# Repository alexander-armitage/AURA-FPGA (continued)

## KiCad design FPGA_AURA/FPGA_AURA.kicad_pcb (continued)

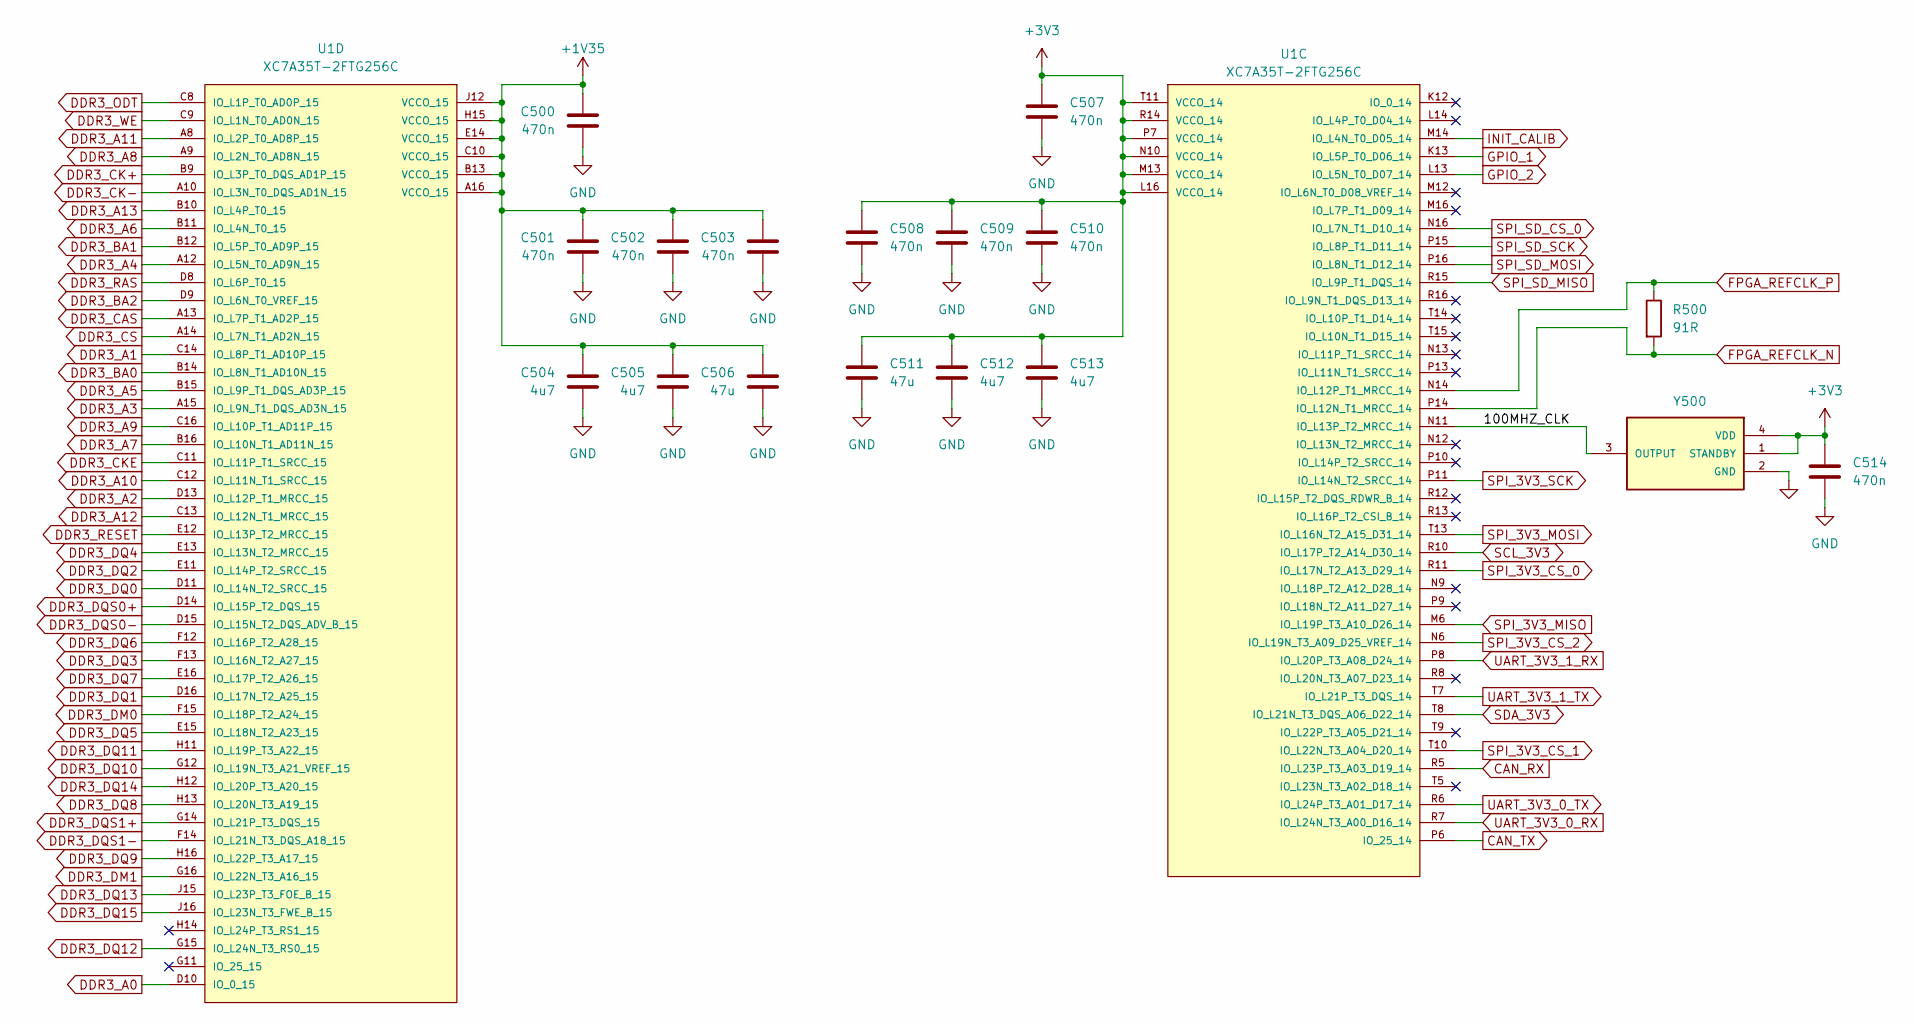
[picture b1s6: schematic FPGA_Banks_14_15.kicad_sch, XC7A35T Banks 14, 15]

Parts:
C500, C501, C502, C503, C507, C508, C509, C510, C514: 470n; C_0402_1005Metric
C504, C505, C512, C513: 4u7; C_0603_1608Metric
C506, C511: 47u; C_0603_1608Metric
R500: 91R; R_0201_0603Metric
U1: XC7A35T-2FTG256C; BGA256C100P16X16_1700X1700X155
Y500: ASEM1-100.000MHZ-LC-T; XTAL_ASEM1-100.000MHZ-LC-T; PARTREV 1.4.2021

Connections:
+1V35: C500.1, C501.1, C502.1, C503.1, C504.1, C505.1, C506.1, U1.A16 (VCCO_15), U1.B13 (VCCO_15), U1.C10 (VCCO_15), U1.E14 (VCCO_15), U1.H15 (VCCO_15), U1.J12 (VCCO_15); also elsewhere on the board
+3V3: C507.1, C508.1, C509.1, C510.1, C511.1, C512.1, C513.1, C514.1, U1.L16 (VCCO_14), U1.M13 (VCCO_14), U1.N10 (VCCO_14), U1.P7 (VCCO_14), U1.R14 (VCCO_14), U1.T11 (VCCO_14), Y500.1 (STANDBY), Y500.4 (VDD); also elsewhere on the board
/500_FPGA_Banks_14_15/100MHZ_CLK: U1.N11 (IO_L13P_T2_MRCC_14), Y500.3 (OUTPUT)
CAN_RX: U1.R5 (IO_L23P_T3_A03_D19_14); also elsewhere on the board
CAN_TX: U1.P6 (IO_25_14); also elsewhere on the board
DDR3_A0: U1.D10 (IO_0_15); also elsewhere on the board
DDR3_A1: U1.C14 (IO_L8P_T1_AD10P_15); also elsewhere on the board
DDR3_A2: U1.D13 (IO_L12P_T1_MRCC_15); also elsewhere on the board
DDR3_A3: U1.A15 (IO_L9N_T1_DQS_AD3N_15); also elsewhere on the board
DDR3_A4: U1.A12 (IO_L5N_T0_AD9N_15); also elsewhere on the board
DDR3_A5: U1.B15 (IO_L9P_T1_DQS_AD3P_15); also elsewhere on the board
DDR3_A6: U1.B11 (IO_L4N_T0_15); also elsewhere on the board
DDR3_A7: U1.B16 (IO_L10N_T1_AD11N_15); also elsewhere on the board
DDR3_A8: U1.A9 (IO_L2N_T0_AD8N_15); also elsewhere on the board
DDR3_A9: U1.C16 (IO_L10P_T1_AD11P_15); also elsewhere on the board
DDR3_A10: U1.C12 (IO_L11N_T1_SRCC_15); also elsewhere on the board
DDR3_A11: U1.A8 (IO_L2P_T0_AD8P_15); also elsewhere on the board
DDR3_A12: U1.C13 (IO_L12N_T1_MRCC_15); also elsewhere on the board
DDR3_A13: U1.B10 (IO_L4P_T0_15); also elsewhere on the board
DDR3_BA0: U1.B14 (IO_L8N_T1_AD10N_15); also elsewhere on the board
DDR3_BA1: U1.B12 (IO_L5P_T0_AD9P_15); also elsewhere on the board
DDR3_BA2: U1.D9 (IO_L6N_T0_VREF_15); also elsewhere on the board
DDR3_CAS: U1.A13 (IO_L7P_T1_AD2P_15); also elsewhere on the board
DDR3_CK+: U1.B9 (IO_L3P_T0_DQS_AD1P_15); also elsewhere on the board
DDR3_CK-: U1.A10 (IO_L3N_T0_DQS_AD1N_15); also elsewhere on the board
DDR3_CKE: U1.C11 (IO_L11P_T1_SRCC_15); also elsewhere on the board
DDR3_CS: U1.A14 (IO_L7N_T1_AD2N_15); also elsewhere on the board
DDR3_DM0: U1.F15 (IO_L18P_T2_A24_15); also elsewhere on the board
DDR3_DM1: U1.G16 (IO_L22N_T3_A16_15); also elsewhere on the board
DDR3_DQ0: U1.D11 (IO_L14N_T2_SRCC_15); also elsewhere on the board
DDR3_DQ1: U1.D16 (IO_L17N_T2_A25_15); also elsewhere on the board
DDR3_DQ2: U1.E11 (IO_L14P_T2_SRCC_15); also elsewhere on the board
DDR3_DQ3: U1.F13 (IO_L16N_T2_A27_15); also elsewhere on the board
DDR3_DQ4: U1.E13 (IO_L13N_T2_MRCC_15); also elsewhere on the board
DDR3_DQ5: U1.E15 (IO_L18N_T2_A23_15); also elsewhere on the board
DDR3_DQ6: U1.F12 (IO_L16P_T2_A28_15); also elsewhere on the board
DDR3_DQ7: U1.E16 (IO_L17P_T2_A26_15); also elsewhere on the board
DDR3_DQ8: U1.H13 (IO_L20N_T3_A19_15); also elsewhere on the board
DDR3_DQ9: U1.H16 (IO_L22P_T3_A17_15); also elsewhere on the board
DDR3_DQ10: U1.G12 (IO_L19N_T3_A21_VREF_15); also elsewhere on the board
DDR3_DQ11: U1.H11 (IO_L19P_T3_A22_15); also elsewhere on the board
DDR3_DQ12: U1.G15 (IO_L24N_T3_RS0_15); also elsewhere on the board
DDR3_DQ13: U1.J15 (IO_L23P_T3_FOE_B_15); also elsewhere on the board
DDR3_DQ14: U1.H12 (IO_L20P_T3_A20_15); also elsewhere on the board
DDR3_DQ15: U1.J16 (IO_L23N_T3_FWE_B_15); also elsewhere on the board
DDR3_DQS0+: U1.D14 (IO_L15P_T2_DQS_15); also elsewhere on the board
DDR3_DQS0-: U1.D15 (IO_L15N_T2_DQS_ADV_B_15); also elsewhere on the board
DDR3_DQS1+: U1.G14 (IO_L21P_T3_DQS_15); also elsewhere on the board
DDR3_DQS1-: U1.F14 (IO_L21N_T3_DQS_A18_15); also elsewhere on the board
DDR3_ODT: U1.C8 (IO_L1P_T0_AD0P_15); also elsewhere on the board
DDR3_RAS: U1.D8 (IO_L6P_T0_15); also elsewhere on the board
DDR3_RESET: U1.E12 (IO_L13P_T2_MRCC_15); also elsewhere on the board
DDR3_WE: U1.C9 (IO_L1N_T0_AD0N_15); also elsewhere on the board
FPGA_REFCLK_N: R500.2, U1.P14 (IO_L12N_T1_MRCC_14); also elsewhere on the board
FPGA_REFCLK_P: R500.1, U1.N14 (IO_L12P_T1_MRCC_14); also elsewhere on the board
GND: C500.2, C501.2, C502.2, C503.2, C504.2, C505.2, C506.2, C507.2, C508.2, C509.2, C510.2, C511.2, C512.2, C513.2, C514.2, Y500.2 (GND); also elsewhere on the board
GPIO_1: U1.K13 (IO_L5P_T0_D06_14); also elsewhere on the board
GPIO_2: U1.L13 (IO_L5N_T0_D07_14); also elsewhere on the board
INIT_CALIB: U1.M14 (IO_L4N_T0_D05_14); also elsewhere on the board
SCL_3V3: U1.R10 (IO_L17P_T2_A14_D30_14); also elsewhere on the board
SDA_3V3: U1.T8 (IO_L21N_T3_DQS_A06_D22_14); also elsewhere on the board
SPI_3V3_CS_0: U1.R11 (IO_L17N_T2_A13_D29_14); also elsewhere on the board
SPI_3V3_CS_1: U1.T10 (IO_L22N_T3_A04_D20_14); also elsewhere on the board
SPI_3V3_CS_2: U1.N6 (IO_L19N_T3_A09_D25_VREF_14); also elsewhere on the board
SPI_3V3_MISO: U1.M6 (IO_L19P_T3_A10_D26_14); also elsewhere on the board
SPI_3V3_MOSI: U1.T13 (IO_L16N_T2_A15_D31_14); also elsewhere on the board
SPI_3V3_SCK: U1.P11 (IO_L14N_T2_SRCC_14); also elsewhere on the board
SPI_SD_CS_0: U1.N16 (IO_L7N_T1_D10_14); also elsewhere on the board
SPI_SD_MISO: U1.R15 (IO_L9P_T1_DQS_14); also elsewhere on the board
SPI_SD_MOSI: U1.P16 (IO_L8N_T1_D12_14); also elsewhere on the board
SPI_SD_SCK: U1.P15 (IO_L8P_T1_D11_14); also elsewhere on the board
UART_3V3_0_RX: U1.R7 (IO_L24N_T3_A00_D16_14); also elsewhere on the board
UART_3V3_0_TX: U1.R6 (IO_L24P_T3_A01_D17_14); also elsewhere on the board
UART_3V3_1_RX: U1.P8 (IO_L20P_T3_A08_D24_14); also elsewhere on the board
UART_3V3_1_TX: U1.T7 (IO_L21P_T3_DQS_14); also elsewhere on the board

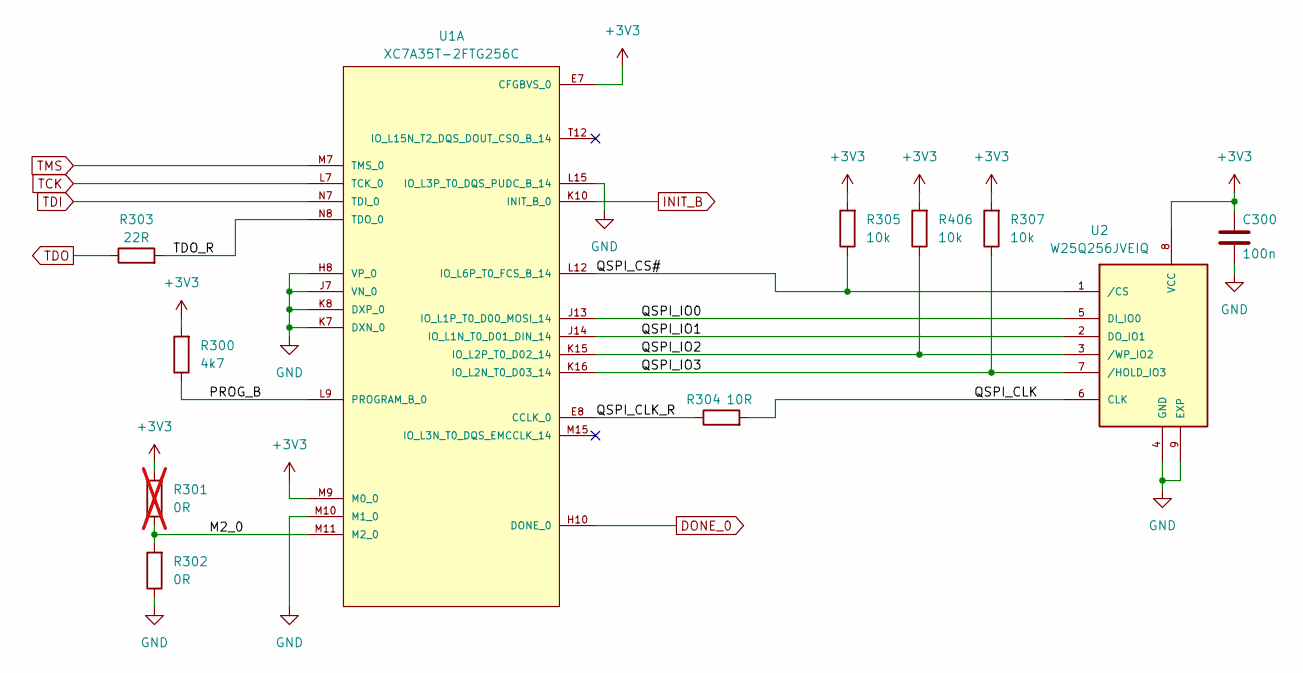
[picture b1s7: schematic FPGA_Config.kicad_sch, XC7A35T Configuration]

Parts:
C300: 100n; C_0402_1005Metric
R300: 4k7; R_0402_1005Metric
R301: 0R; R_0402_1005Metric; not fitted
R302: 0R; R_0402_1005Metric
R303: 22R; R_0402_1005Metric
R304: 10R; R_0402_1005Metric
R305, R307, R406: 10k; R_0402_1005Metric
U1: XC7A35T-2FTG256C; BGA256C100P16X16_1700X1700X155
U2: W25Q256JVEIQ; SON127P800X600X80-9N; MOUSER_PART_NUMBER 454-W25Q256JVEIQ

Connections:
+3V3: C300.1, R300.2, R301.2, R305.2, R307.2, R406.2, U1.E7 (CFGBVS_0), U1.M9 (M0_0), U2.8 (VCC); also elsewhere on the board
/300_FPGA_Config/M2_0: R301.1, R302.2, U1.M11 (M2_0)
/300_FPGA_Config/PROG_B: R300.1, U1.L9 (PROGRAM_B_0)
/300_FPGA_Config/QSPI_CLK: R304.2, U2.6 (CLK)
/300_FPGA_Config/QSPI_CLK_R: R304.1, U1.E8 (CCLK_0)
/300_FPGA_Config/QSPI_CS#: R305.1, U1.L12 (IO_L6P_T0_FCS_B_14), U2.1 (/CS)
/300_FPGA_Config/QSPI_IO0: U1.J13 (IO_L1P_T0_D00_MOSI_14), U2.5 (DI_IO0)
/300_FPGA_Config/QSPI_IO1: U1.J14 (IO_L1N_T0_D01_DIN_14), U2.2 (DO_IO1)
/300_FPGA_Config/QSPI_IO2: R406.1, U1.K15 (IO_L2P_T0_D02_14), U2.3 (/WP_IO2)
/300_FPGA_Config/QSPI_IO3: R307.1, U1.K16 (IO_L2N_T0_D03_14), U2.7 (/HOLD_IO3)
/300_FPGA_Config/TDO_R: R303.2, U1.N8 (TDO_0)
DONE_0: U1.H10 (DONE_0); also elsewhere on the board
GND: C300.2, R302.1, U1.H8 (VP_0), U1.J7 (VN_0), U1.K7 (DXN_0), U1.K8 (DXP_0), U1.L15 (IO_L3P_T0_DQS_PUDC_B_14), U1.M10 (M1_0), U2.4 (GND), U2.9 (EXP); also elsewhere on the board
INIT_B: U1.K10 (INIT_B_0); also elsewhere on the board
TCK: U1.L7 (TCK_0); also elsewhere on the board
TDI: U1.N7 (TDI_0); also elsewhere on the board
TDO: R303.1; also elsewhere on the board
TMS: U1.M7 (TMS_0); also elsewhere on the board

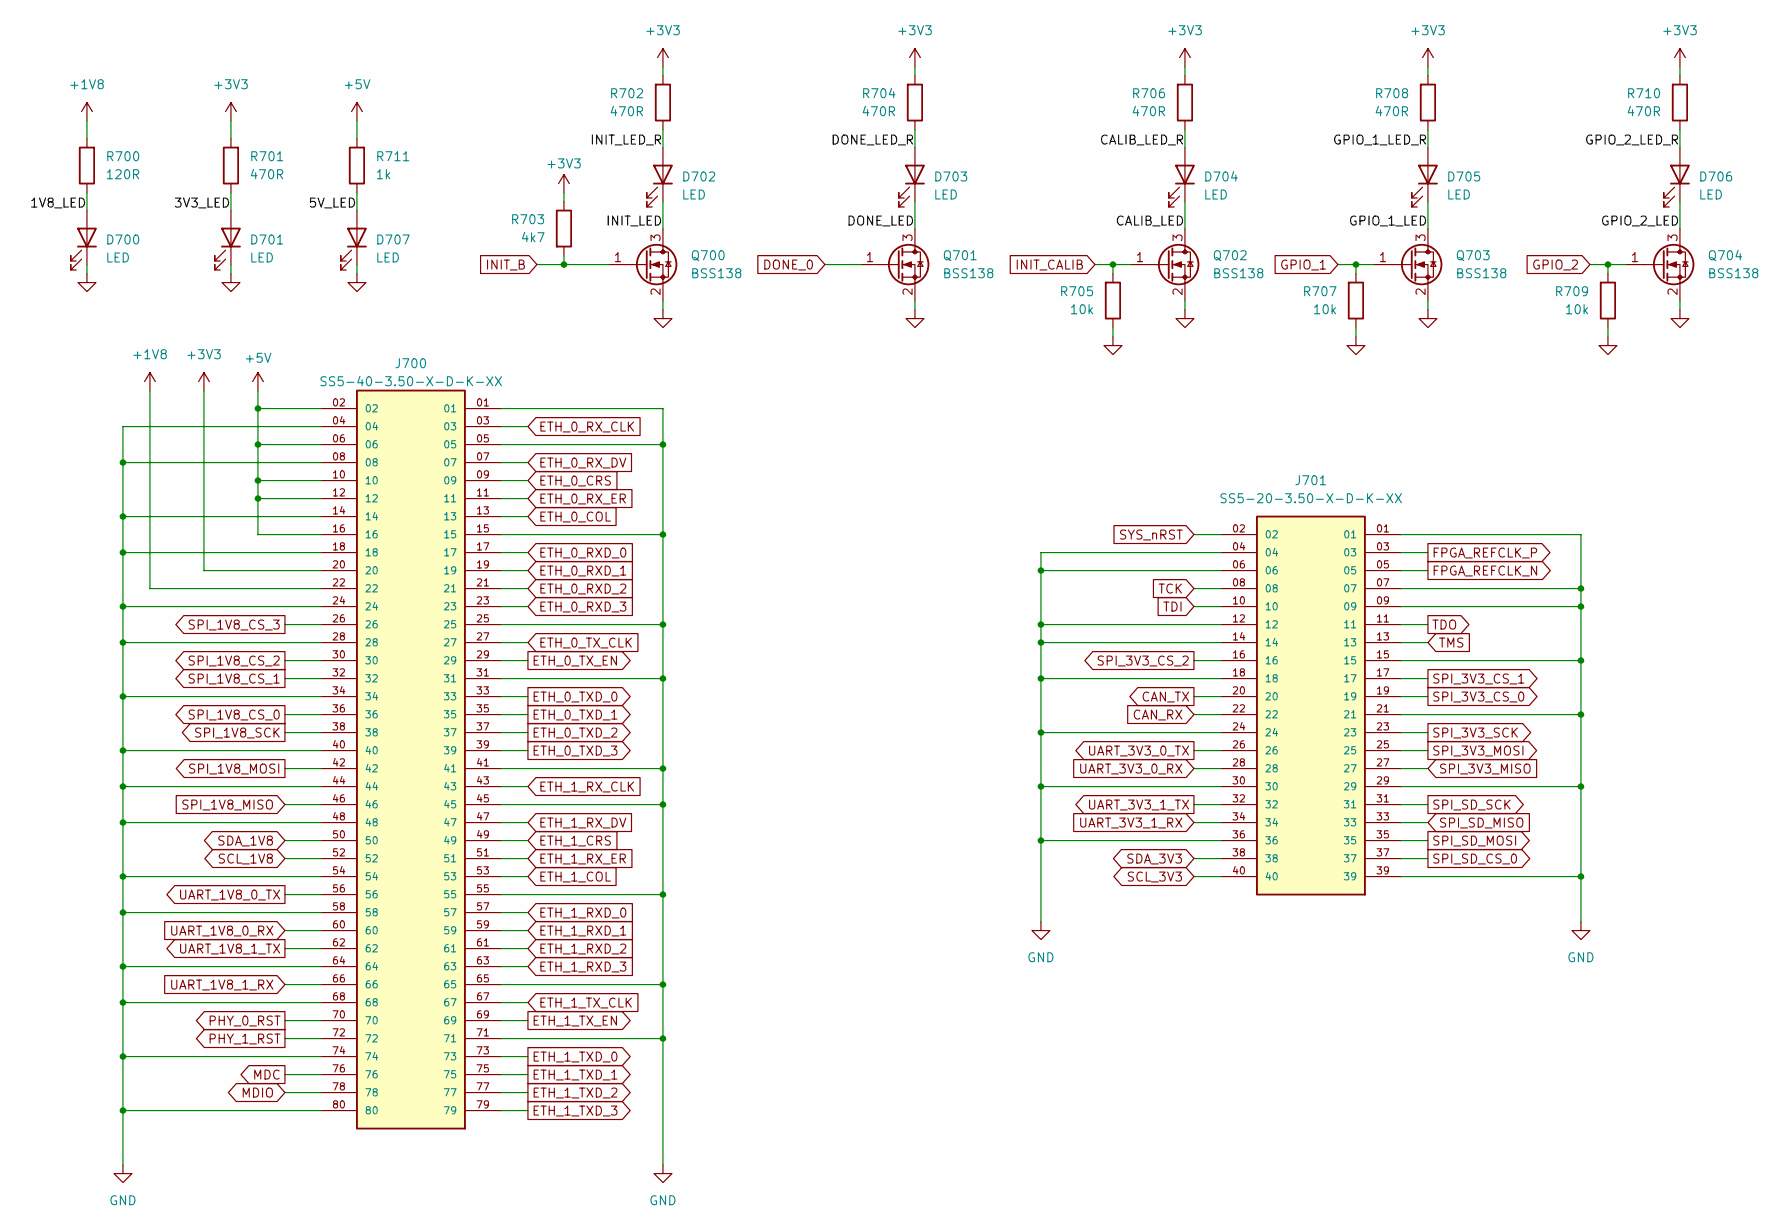
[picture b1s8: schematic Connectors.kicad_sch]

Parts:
D700, D701, D702, D703, D704, D705, D706, D707: LED; LED_0603_1608Metric
J700: SS5-40-3.50-X-D-K-XX; SAMTEC_SS5-40-3.50-X-D-K-XX; PARTREV F
J701: SS5-20-3.50-X-D-K-XX; SAMTEC_SS5-20-3.50-X-D-K-XX; PARTREV F
Q700, Q701, Q702, Q703, Q704: BSS138; SOT-23
R700: 120R; R_0402_1005Metric
R701, R702, R704, R706, R708, R710: 470R; R_0402_1005Metric
R703: 4k7; R_0402_1005Metric
R705, R707, R709: 10k; R_0402_1005Metric
R711: 1k; R_0402_1005Metric

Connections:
+1V8: J700.22, R700.2; also elsewhere on the board
+3V3: J700.20, R701.2, R702.2, R703.1, R704.2, R706.2, R708.2, R710.2; also elsewhere on the board
+5V: J700.02, J700.06, J700.10, J700.12, J700.16, R711.2; also elsewhere on the board
/700_Connectors/1V8_LED: D700.2 (A), R700.1
/700_Connectors/3V3_LED: D701.2 (A), R701.1
/700_Connectors/5V_LED: D707.2 (A), R711.1
/700_Connectors/CALIB_LED: D704.1 (K), Q702.3 (D)
/700_Connectors/CALIB_LED_R: D704.2 (A), R706.1
/700_Connectors/DONE_LED: D703.1 (K), Q701.3 (D)
/700_Connectors/DONE_LED_R: D703.2 (A), R704.1
/700_Connectors/GPIO_1_LED: D705.1 (K), Q703.3 (D)
/700_Connectors/GPIO_1_LED_R: D705.2 (A), R708.1
/700_Connectors/GPIO_2_LED: D706.1 (K), Q704.3 (D)
/700_Connectors/GPIO_2_LED_R: D706.2 (A), R710.1
/700_Connectors/INIT_LED: D702.1 (K), Q700.3 (D)
/700_Connectors/INIT_LED_R: D702.2 (A), R702.1
CAN_RX: J701.22; also elsewhere on the board
CAN_TX: J701.20; also elsewhere on the board
DONE_0: Q701.1 (G); also elsewhere on the board
ETH_0_COL: J700.13; also elsewhere on the board
ETH_0_CRS: J700.09; also elsewhere on the board
ETH_0_RXD_0: J700.17; also elsewhere on the board
ETH_0_RXD_1: J700.19; also elsewhere on the board
ETH_0_RXD_2: J700.21; also elsewhere on the board
ETH_0_RXD_3: J700.23; also elsewhere on the board
ETH_0_RX_CLK: J700.03; also elsewhere on the board
ETH_0_RX_DV: J700.07; also elsewhere on the board
ETH_0_RX_ER: J700.11; also elsewhere on the board
ETH_0_TXD_0: J700.33; also elsewhere on the board
ETH_0_TXD_1: J700.35; also elsewhere on the board
ETH_0_TXD_2: J700.37; also elsewhere on the board
ETH_0_TXD_3: J700.39; also elsewhere on the board
ETH_0_TX_CLK: J700.27; also elsewhere on the board
ETH_0_TX_EN: J700.29; also elsewhere on the board
ETH_1_COL: J700.53; also elsewhere on the board
ETH_1_CRS: J700.49; also elsewhere on the board
ETH_1_RXD_0: J700.57; also elsewhere on the board
ETH_1_RXD_1: J700.59; also elsewhere on the board
ETH_1_RXD_2: J700.61; also elsewhere on the board
ETH_1_RXD_3: J700.63; also elsewhere on the board
ETH_1_RX_CLK: J700.43; also elsewhere on the board
ETH_1_RX_DV: J700.47; also elsewhere on the board
ETH_1_RX_ER: J700.51; also elsewhere on the board
ETH_1_TXD_0: J700.73; also elsewhere on the board
ETH_1_TXD_1: J700.75; also elsewhere on the board
ETH_1_TXD_2: J700.77; also elsewhere on the board
ETH_1_TXD_3: J700.79; also elsewhere on the board
ETH_1_TX_CLK: J700.67; also elsewhere on the board
ETH_1_TX_EN: J700.69; also elsewhere on the board
FPGA_REFCLK_N: J701.05; also elsewhere on the board
FPGA_REFCLK_P: J701.03; also elsewhere on the board
GND: D700.1 (K), D701.1 (K), D707.1 (K), J700.01, J700.04, J700.05, J700.08, J700.14, J700.15, J700.18, J700.24, J700.25, J700.28, J700.31, J700.34, J700.40, J700.41, J700.44, J700.45, J700.48, J700.54, J700.55, J700.58, J700.64, J700.65, J700.68, J700.71, J700.74, J700.80, J701.01, J701.04, J701.06, J701.07, J701.09, J701.12, J701.14, J701.15, J701.18, J701.21, J701.24, J701.29, J701.30, J701.36, J701.39, Q700.2 (S), Q701.2 (S), Q702.2 (S), Q703.2 (S), Q704.2 (S), R705.1, R707.1, R709.1; also elsewhere on the board
GPIO_1: Q703.1 (G), R707.2; also elsewhere on the board
GPIO_2: Q704.1 (G), R709.2; also elsewhere on the board
INIT_B: Q700.1 (G), R703.2; also elsewhere on the board
INIT_CALIB: Q702.1 (G), R705.2; also elsewhere on the board
MDC: J700.76; also elsewhere on the board
MDIO: J700.78; also elsewhere on the board
PHY_0_RST: J700.70; also elsewhere on the board
PHY_1_RST: J700.72; also elsewhere on the board
SCL_1V8: J700.52; also elsewhere on the board
SCL_3V3: J701.40; also elsewhere on the board
SDA_1V8: J700.50; also elsewhere on the board
SDA_3V3: J701.38; also elsewhere on the board
SPI_1V8_CS_0: J700.36; also elsewhere on the board
SPI_1V8_CS_1: J700.32; also elsewhere on the board
SPI_1V8_CS_2: J700.30; also elsewhere on the board
SPI_1V8_CS_3: J700.26; also elsewhere on the board
SPI_1V8_MISO: J700.46; also elsewhere on the board
SPI_1V8_MOSI: J700.42; also elsewhere on the board
SPI_1V8_SCK: J700.38; also elsewhere on the board
SPI_3V3_CS_0: J701.19; also elsewhere on the board
SPI_3V3_CS_1: J701.17; also elsewhere on the board
SPI_3V3_CS_2: J701.16; also elsewhere on the board
SPI_3V3_MISO: J701.27; also elsewhere on the board
SPI_3V3_MOSI: J701.25; also elsewhere on the board
SPI_3V3_SCK: J701.23; also elsewhere on the board
SPI_SD_CS_0: J701.37; also elsewhere on the board
SPI_SD_MISO: J701.33; also elsewhere on the board
SPI_SD_MOSI: J701.35; also elsewhere on the board
SPI_SD_SCK: J701.31; also elsewhere on the board
SYS_nRST: J701.02; also elsewhere on the board
TCK: J701.08; also elsewhere on the board
TDI: J701.10; also elsewhere on the board
TDO: J701.11; also elsewhere on the board
TMS: J701.13; also elsewhere on the board
UART_1V8_0_RX: J700.60; also elsewhere on the board
UART_1V8_0_TX: J700.56; also elsewhere on the board
UART_1V8_1_RX: J700.66; also elsewhere on the board
UART_1V8_1_TX: J700.62; also elsewhere on the board
UART_3V3_0_RX: J701.28; also elsewhere on the board
UART_3V3_0_TX: J701.26; also elsewhere on the board
UART_3V3_1_RX: J701.34; also elsewhere on the board
UART_3V3_1_TX: J701.32; also elsewhere on the board

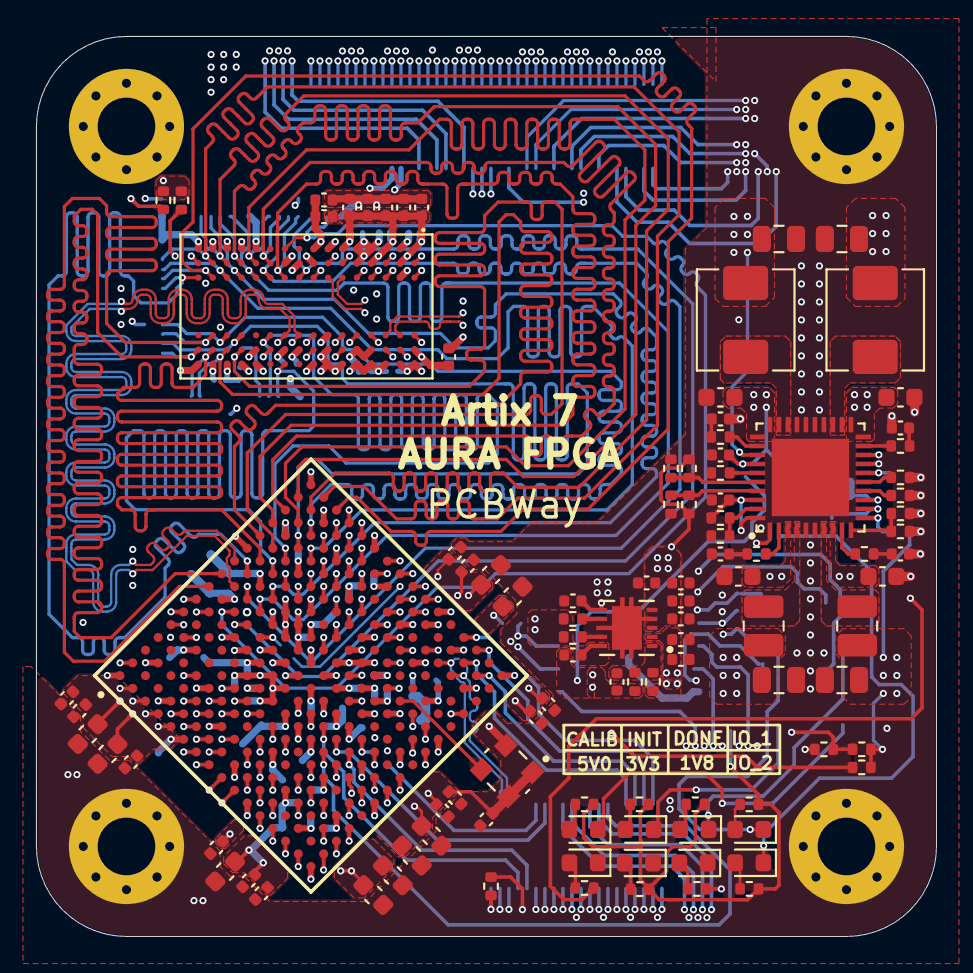
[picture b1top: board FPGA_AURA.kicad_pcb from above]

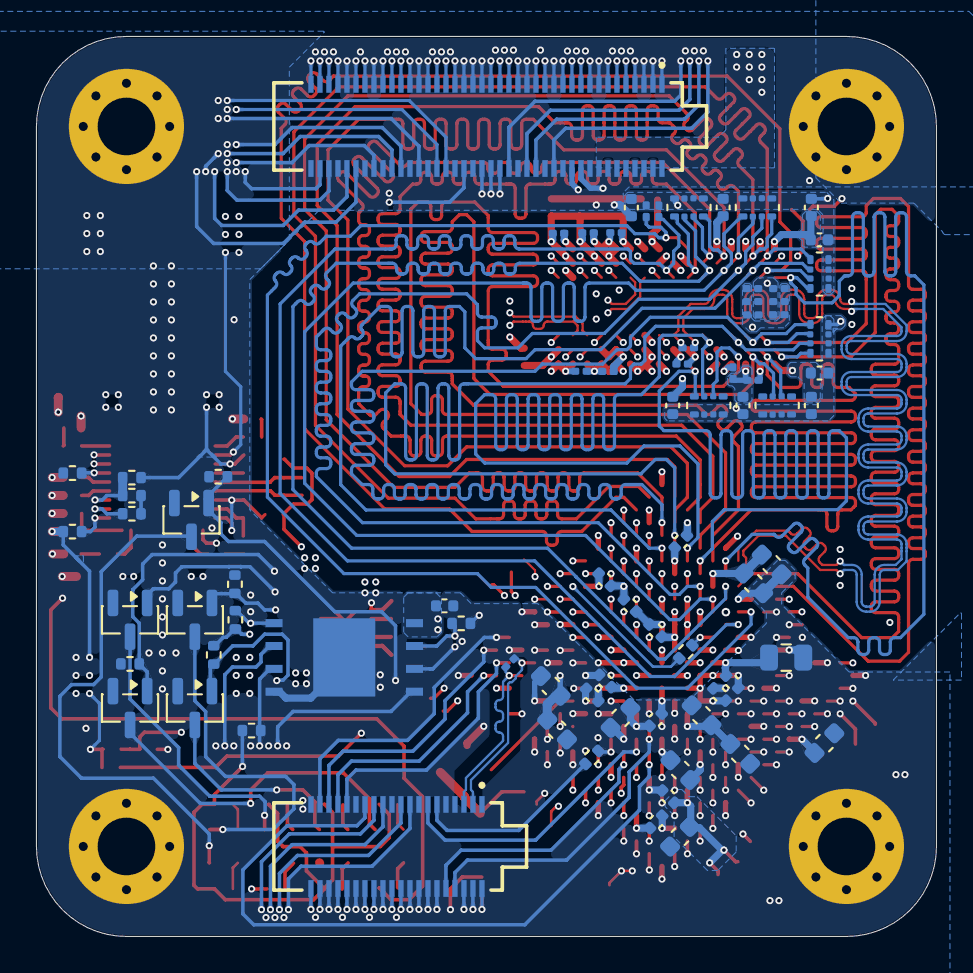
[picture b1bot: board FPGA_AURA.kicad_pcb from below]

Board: 10 copper layers, 50.0 x 50.0 mm, 184 parts (77 on the bottom side), 185 nets.

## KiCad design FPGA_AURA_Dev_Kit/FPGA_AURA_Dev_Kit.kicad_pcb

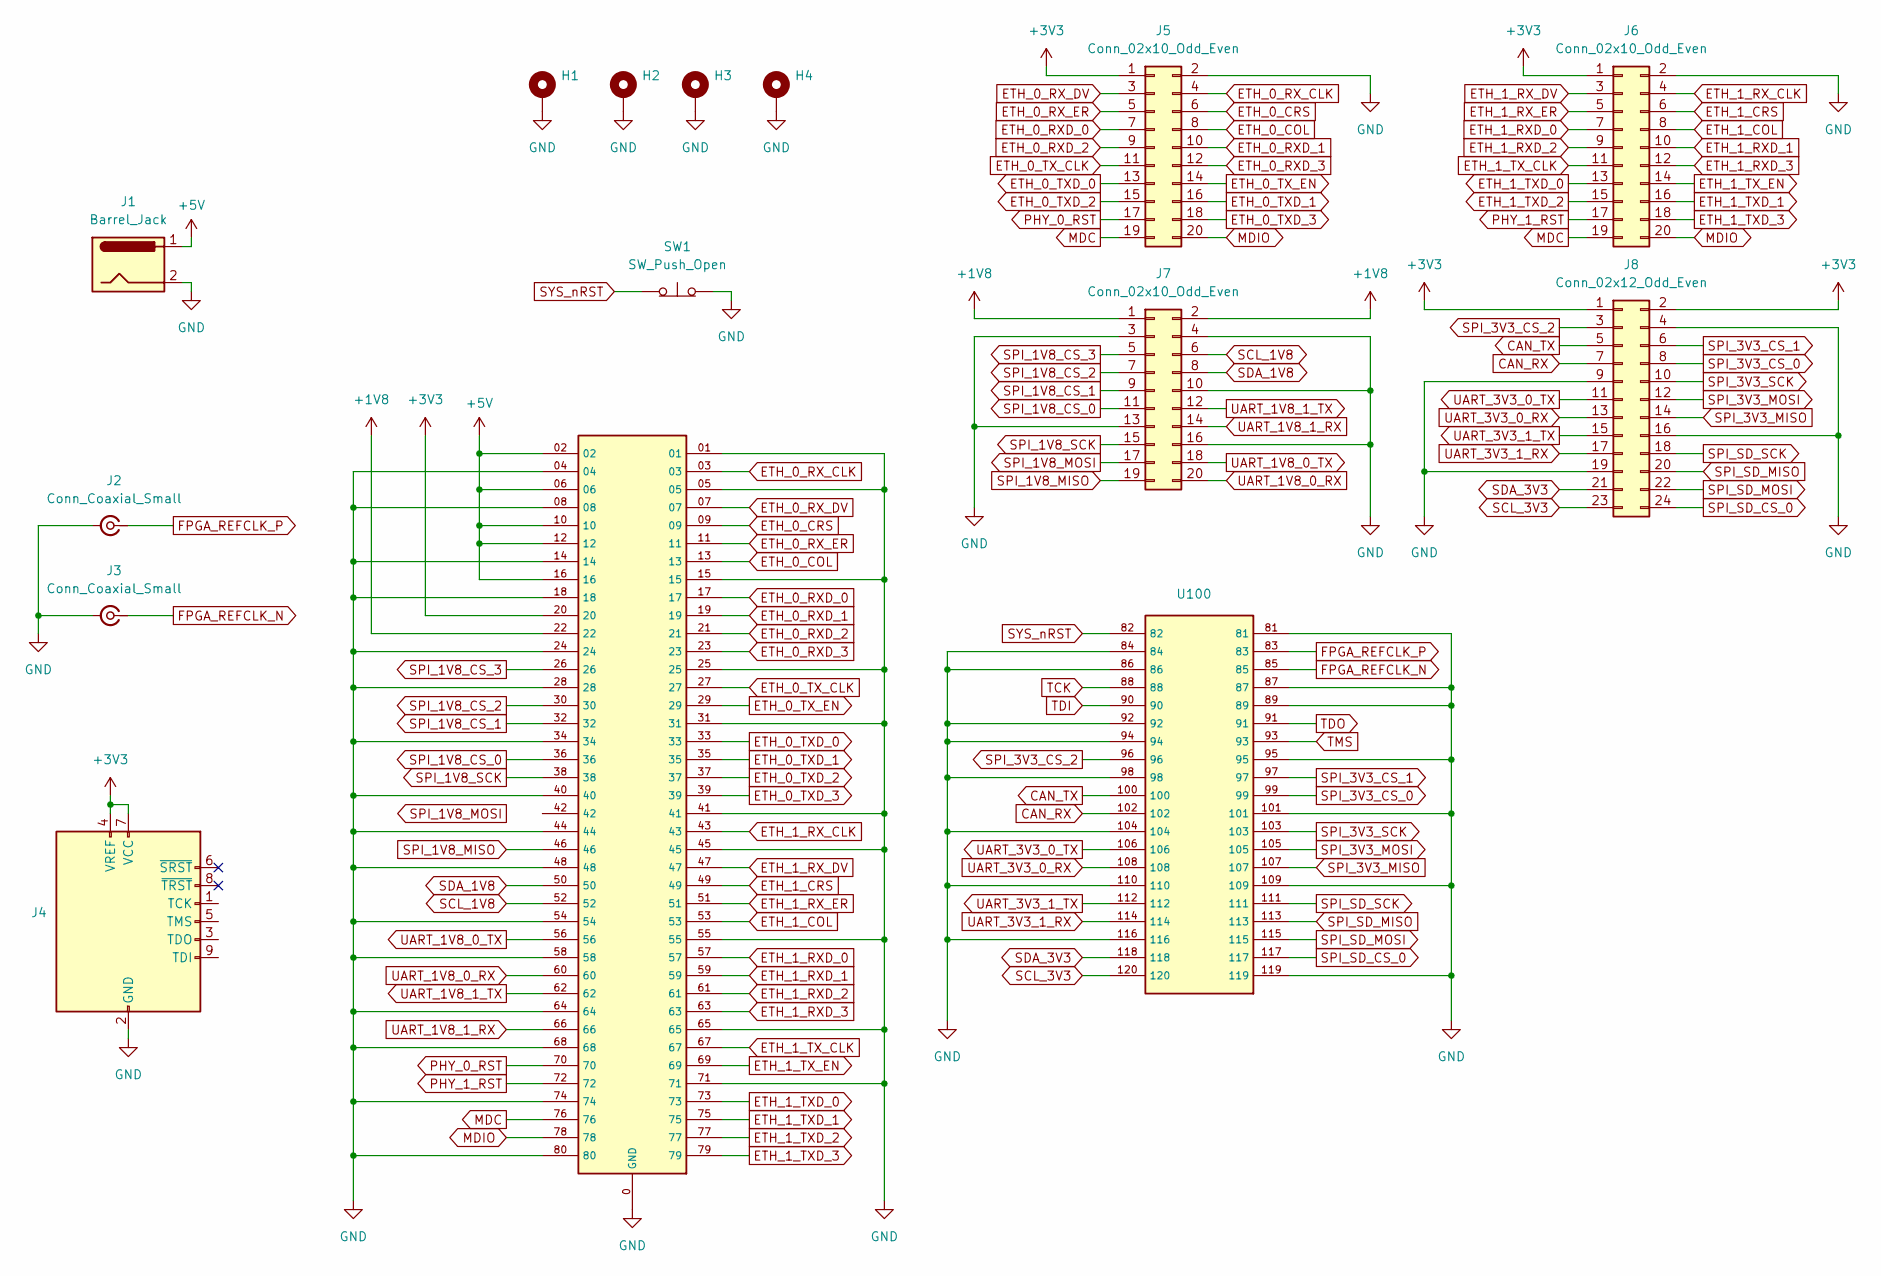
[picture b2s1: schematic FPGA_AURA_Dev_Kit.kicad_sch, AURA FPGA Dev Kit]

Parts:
H1, H2, H3, H4: MountingHole_Pad; MountingHole_3.2mm_M3_Pad_Via
J1: Barrel_Jack; BarrelJack_GCT_DCJ200-10-A_Horizontal
J2, J3: Conn_Coaxial_Small; SMA_Wurth_60312102114405_Vertical
J4: AVR-JTAG-10; SAMESKY_SSK05-BH-254-B5
J5, J6, J7: Conn_02x10_Odd_Even; PinHeader_2x10_P2.54mm_Vertical
J8: Conn_02x12_Odd_Even; PinHeader_2x12_P2.54mm_Vertical
SW1: SW_Push_Open; SW_SPST_CK_RS282G05A3
U100: AURA-FPGA

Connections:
+1V8: J7.1, J7.2, U100.22
+3V3: J4.4 (VREF), J4.7 (VCC), J5.1, J6.1, J8.1, J8.2, U100.20
+5V: J1.1, U100.02, U100.06, U100.10, U100.12, U100.16
CAN_RX: J8.7, U100.102
CAN_TX: J8.5, U100.100
ETH_0_COL: J5.8, U100.13
ETH_0_CRS: J5.6, U100.09
ETH_0_RXD_0: J5.7, U100.17
ETH_0_RXD_1: J5.10, U100.19
ETH_0_RXD_2: J5.9, U100.21
ETH_0_RXD_3: J5.12, U100.23
ETH_0_RX_CLK: J5.4, U100.03
ETH_0_RX_DV: J5.3, U100.07
ETH_0_RX_ER: J5.5, U100.11
ETH_0_TXD_0: J5.13, U100.33
ETH_0_TXD_1: J5.16, U100.35
ETH_0_TXD_2: J5.15, U100.37
ETH_0_TXD_3: J5.18, U100.39
ETH_0_TX_CLK: J5.11, U100.27
ETH_0_TX_EN: J5.14, U100.29
ETH_1_COL: J6.8, U100.53
ETH_1_CRS: J6.6, U100.49
ETH_1_RXD_0: J6.7, U100.57
ETH_1_RXD_1: J6.10, U100.59
ETH_1_RXD_2: J6.9, U100.61
ETH_1_RXD_3: J6.12, U100.63
ETH_1_RX_CLK: J6.4, U100.43
ETH_1_RX_DV: J6.3, U100.47
ETH_1_RX_ER: J6.5, U100.51
ETH_1_TXD_0: J6.13, U100.73
ETH_1_TXD_1: J6.16, U100.75
ETH_1_TXD_2: J6.15, U100.77
ETH_1_TXD_3: J6.18, U100.79
ETH_1_TX_CLK: J6.11, U100.67
ETH_1_TX_EN: J6.14, U100.69
FPGA_REFCLK_N: J3.1 (In), U100.85
FPGA_REFCLK_P: J2.1 (In), U100.83
GND: H1.1 (1_1), H2.1 (1_1), H3.1 (1_1), H4.1 (1_1), J1.2, J2.2 (Ext), J3.2 (Ext), J4.2 (GND), J4.10 (GND), J5.2, J6.2, J7.3, J7.4, J7.10, J7.13, J7.16, J8.4, J8.9, J8.16, J8.19, SW1.2 (B), U100.0 (GND), U100.01, U100.04, U100.05, U100.08, U100.14, U100.15, U100.18, U100.24, U100.25, U100.28, U100.31, U100.34, U100.40, U100.41, U100.44, U100.45, U100.48, U100.54, U100.55, U100.58, U100.64, U100.65, U100.68, U100.71, U100.74, U100.80, U100.81, U100.84, U100.86, U100.87, U100.89, U100.92, U100.94, U100.95, U100.98, U100.101, U100.104, U100.109, U100.110, U100.116, U100.119
MDC: J5.19, J6.19, U100.76
MDIO: J5.20, J6.20, U100.78
PHY_0_RST: J5.17, U100.70
PHY_1_RST: J6.17, U100.72
SCL_1V8: J7.6, U100.52
SCL_3V3: J8.23, U100.120
SDA_1V8: J7.8, U100.50
SDA_3V3: J8.21, U100.118
SPI_1V8_CS_0: J7.11, U100.36
SPI_1V8_CS_1: J7.9, U100.32
SPI_1V8_CS_2: J7.7, U100.30
SPI_1V8_CS_3: J7.5, U100.26
SPI_1V8_MISO: J7.19, U100.46
SPI_1V8_MOSI: J7.17
SPI_1V8_SCK: J7.15, U100.38
SPI_3V3_CS_0: J8.8, U100.99
SPI_3V3_CS_1: J8.6, U100.97
SPI_3V3_CS_2: J8.3, U100.96
SPI_3V3_MISO: J8.14, U100.107
SPI_3V3_MOSI: J8.12, U100.105
SPI_3V3_SCK: J8.10, U100.103
SPI_SD_CS_0: J8.24, U100.117
SPI_SD_MISO: J8.20, U100.113
SPI_SD_MOSI: J8.22, U100.115
SPI_SD_SCK: J8.18, U100.111
SYS_nRST: SW1.1 (A), U100.82
TCK: U100.88
TDI: U100.90
TDO: U100.91
TMS: U100.93
UART_1V8_0_RX: J7.20, U100.60
UART_1V8_0_TX: J7.18, U100.56
UART_1V8_1_RX: J7.14, U100.66
UART_1V8_1_TX: J7.12, U100.62
UART_3V3_0_RX: J8.13, U100.108
UART_3V3_0_TX: J8.11, U100.106
UART_3V3_1_RX: J8.17, U100.114
UART_3V3_1_TX: J8.15, U100.112

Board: 4 copper layers, 14 parts (0 on the bottom side), 71 nets, no tracks yet.
